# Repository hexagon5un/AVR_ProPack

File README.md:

# AVR ProPack

(rhymes with Kropak.  Yummm...)

## Simple Circuit Bits to Help Your Breadboarding

Preliminary docs up at http://littlehacks.org/propack

At the moment, everything's in a state of beta.  You're welcome to try anything out.

I'm going to make a run of these boards soon enough in the future.  If you're interested, let me know.

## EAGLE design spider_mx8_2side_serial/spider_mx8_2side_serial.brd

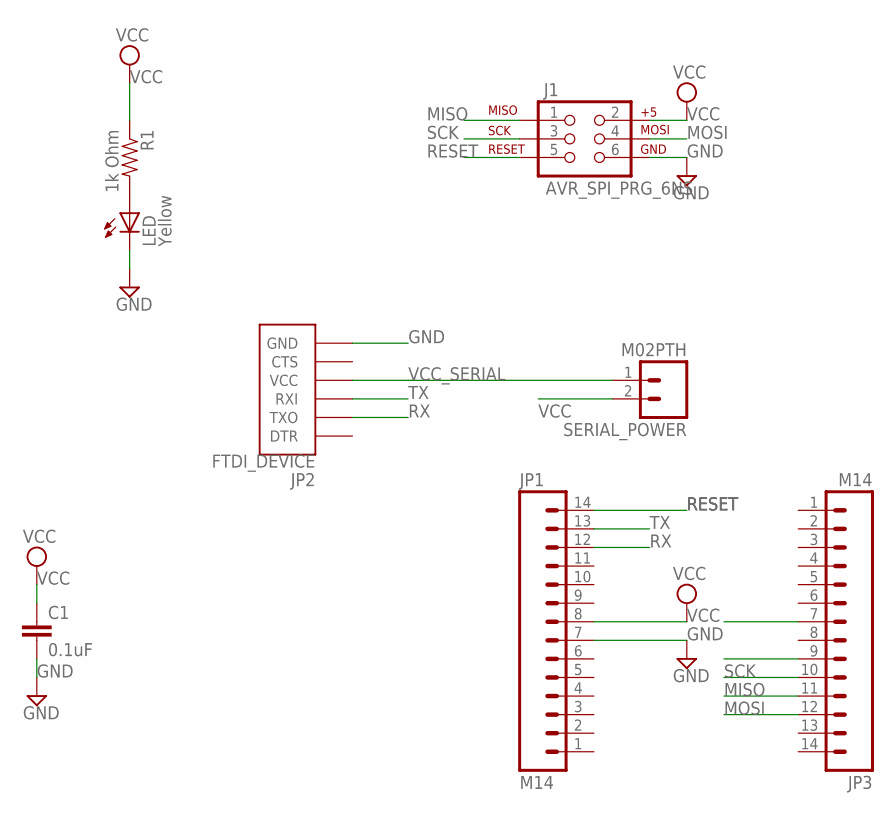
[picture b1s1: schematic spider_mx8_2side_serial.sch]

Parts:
C1: 0.1uF; 1206
J1: AVR_SPI_PRG_6NS; 2X3-NS
JP1, JP3: M14; 1X14
JP2: FTDI_DEVICE; FTDI_DEVICE_SIDE
LED: Yellow; LED-1206
R1: 1k Ohm; 1206
SERIAL_POWER: M02PTH; 1X02

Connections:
GND: C1.2, J1.6, JP1.7, JP2.P$6 (GND), JP3.7, LED.C
MISO: J1.1, JP3.11
MOSI: J1.4, JP3.12
unnamed: LED.A, R1.2
RESET: J1.5, JP1.14
RX: JP1.12, JP2.P$2 (TXO)
SCK: J1.3, JP3.10
TX: JP1.13, JP2.P$3 (RXI)
VCC: C1.1, J1.2, JP1.8, JP3.9, R1.1, SERIAL_POWER.2
VCC_SERIAL: JP2.P$4 (VCC), SERIAL_POWER.1

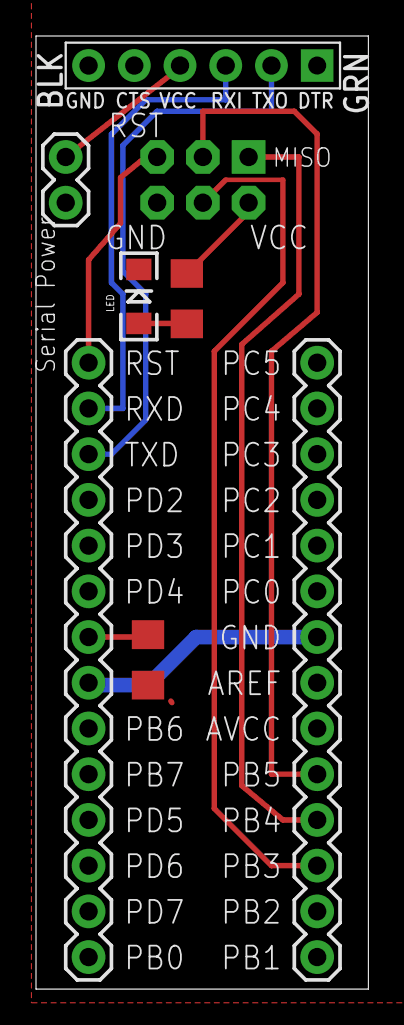
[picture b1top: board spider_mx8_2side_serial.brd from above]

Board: 2 copper layers, 18.5 x 52.9 mm, 8 parts (0 on the bottom side), 10 nets.

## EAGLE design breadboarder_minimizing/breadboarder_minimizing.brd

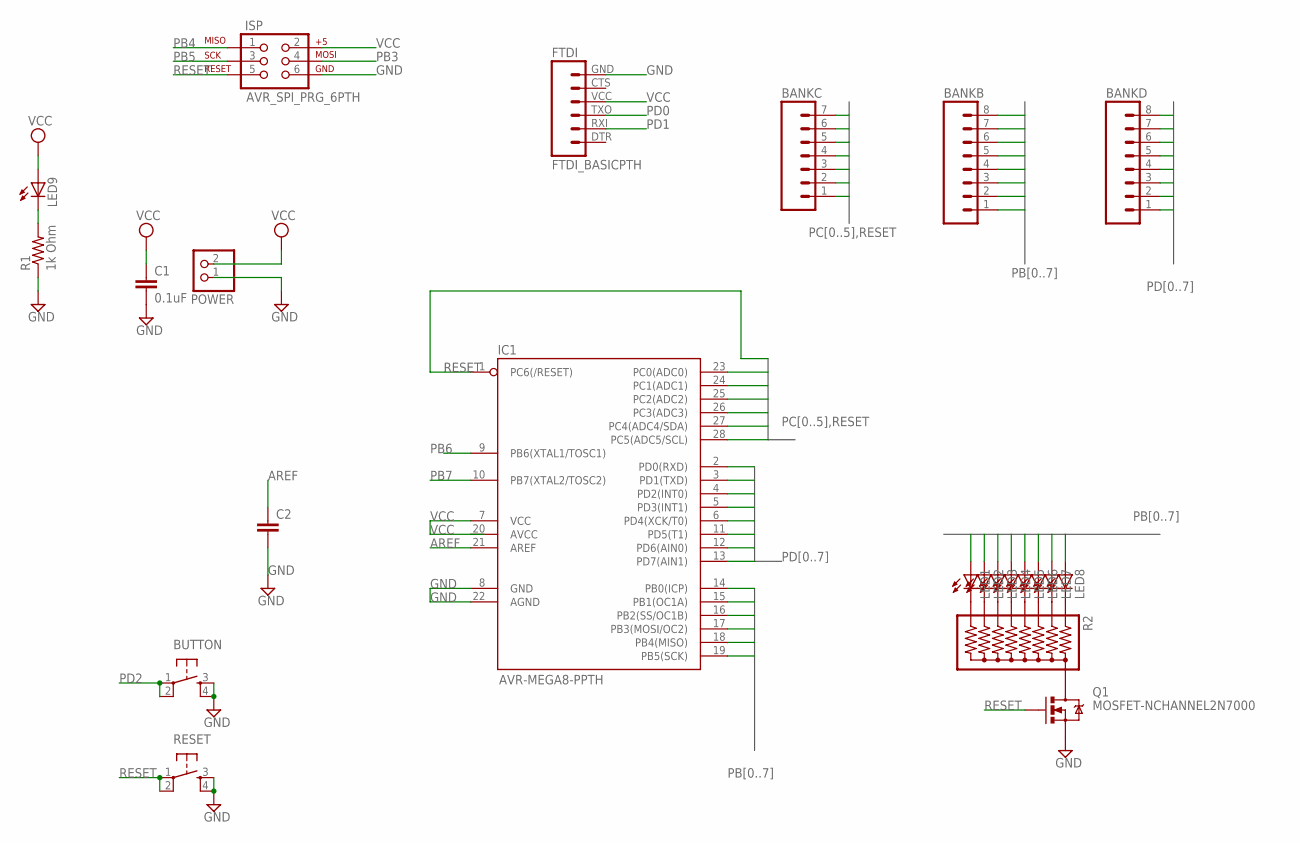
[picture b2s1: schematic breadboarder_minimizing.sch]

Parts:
BANKB: M08LONGPADS; 1X08_LONGPADS
BANKC: M07LONGPADS; 1X07_LONGPADS
BANKD: M08LONGPADS; 1X08_LONGPADS
BUTTON: TAC_SWITCHPTH; TACTILE-PTH
C1: 0.1uF; CAP-PTH-SMALL-KIT
C2: CAPKIT; CAP-PTH-SMALL-KIT
FTDI: FTDI_BASICPTH; FTDI_BASIC
IC1: AVR-MEGA8-PPTH; DIL28-3
ISP: AVR_SPI_PRG_6PTH; 2X3
LED1, LED2, LED3, LED4, LED5, LED6, LED7, LED8, LED9: LED3MM
POWER: PINHD-1X2; 1X02
Q1: MOSFET-NCHANNEL2N7000; TO-92
R1: 1k Ohm; AXIAL-0.3
R2: RPACK-BUSSED-8SIP-PTH-8-LP; RPACK-SIP-PTH-8-LP
RESET: TAC_SWITCHPTH; TACTILE-PTH

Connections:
AREF: C2.1, IC1.21 (AREF)
GND: BUTTON.3, BUTTON.4, C1.2, C2.2, FTDI.GND (6), IC1.8 (GND), IC1.22 (AGND), ISP.6, POWER.1, Q1.1 (S), R1.P$1 (1), RESET.3, RESET.4
unnamed: Q1.3 (D), R2.P$1 (1)
unnamed: LED1.K (C), R2.P$9 (9)
unnamed: LED2.K (C), R2.P$8 (8)
unnamed: LED3.K (C), R2.P$7 (7)
unnamed: LED4.K (C), R2.P$6 (6)
unnamed: LED5.K (C), R2.P$5 (5)
unnamed: LED6.K (C), R2.P$4 (4)
unnamed: LED7.K (C), R2.P$3 (3)
unnamed: LED8.K (C), R2.P$2 (2)
unnamed: LED9.K (C), R1.P$2 (2)
PB0: BANKB.8, IC1.14 (PB0(ICP)), LED1.A
PB1: BANKB.7, IC1.15 (PB1(OC1A)), LED2.A
PB2: BANKB.6, IC1.16 (PB2(SS/OC1B)), LED3.A
PB3: BANKB.5, IC1.17 (PB3(MOSI/OC2)), ISP.4, LED4.A
PB4: BANKB.4, IC1.18 (PB4(MISO)), ISP.1, LED5.A
PB5: BANKB.3, IC1.19 (PB5(SCK)), ISP.3, LED6.A
PB6: BANKB.2, IC1.9 (PB6(XTAL1/TOSC1)), LED7.A
PB7: BANKB.1, IC1.10 (PB7(XTAL2/TOSC2)), LED8.A
PC0: BANKC.7, IC1.23 (PC0(ADC0))
PC1: BANKC.6, IC1.24 (PC1(ADC1))
PC2: BANKC.5, IC1.25 (PC2(ADC2))
PC3: BANKC.4, IC1.26 (PC3(ADC3))
PC4: BANKC.3, IC1.27 (PC4(ADC4/SDA))
PC5: BANKC.2, IC1.28 (PC5(ADC5/SCL))
PD0: BANKD.8, FTDI.TXO (3), IC1.2 (PD0(RXD))
PD1: BANKD.7, FTDI.RXI (2), IC1.3 (PD1(TXD))
PD2: BANKD.6, BUTTON.1, BUTTON.2, IC1.4 (PD2(INT0))
PD3: BANKD.5, IC1.5 (PD3(INT1))
PD4: BANKD.4, IC1.6 (PD4(XCK/T0))
PD5: BANKD.3, IC1.11 (PD5(T1))
PD6: BANKD.2, IC1.12 (PD6(AIN0))
PD7: BANKD.1, IC1.13 (PD7(AIN1))
RESET: BANKC.1, IC1.1 (PC6(/RESET)), ISP.5, Q1.2 (G), RESET.1, RESET.2
VCC: C1.1, FTDI.VCC (4), IC1.7 (VCC), ISP.2, LED9.A, POWER.2

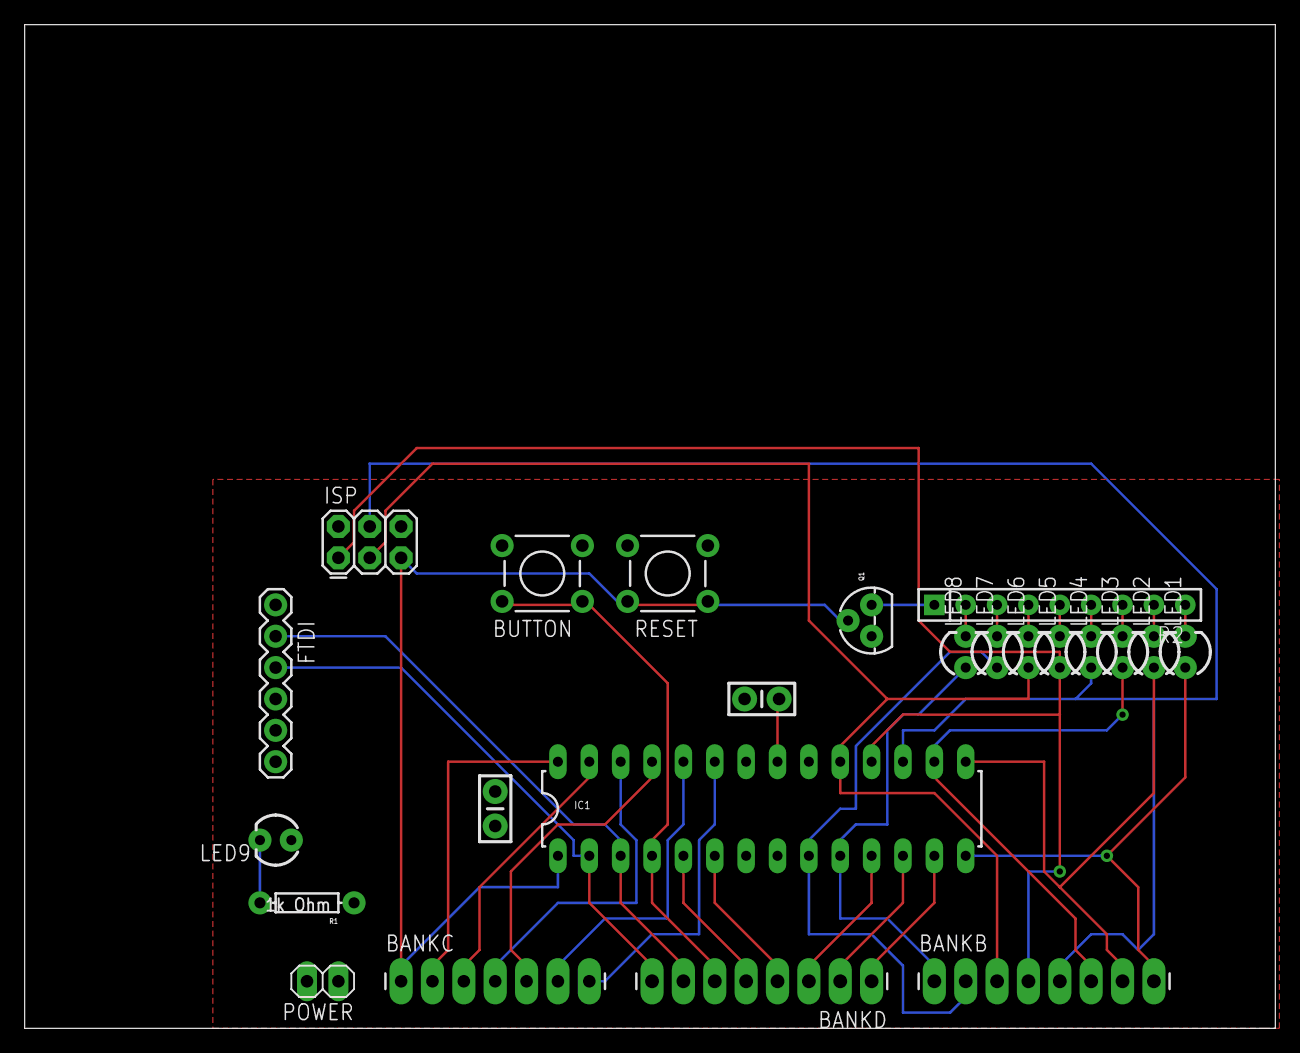
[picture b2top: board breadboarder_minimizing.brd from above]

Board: 2 copper layers, 101.3 x 81.3 mm, 23 parts (0 on the bottom side), 36 nets.

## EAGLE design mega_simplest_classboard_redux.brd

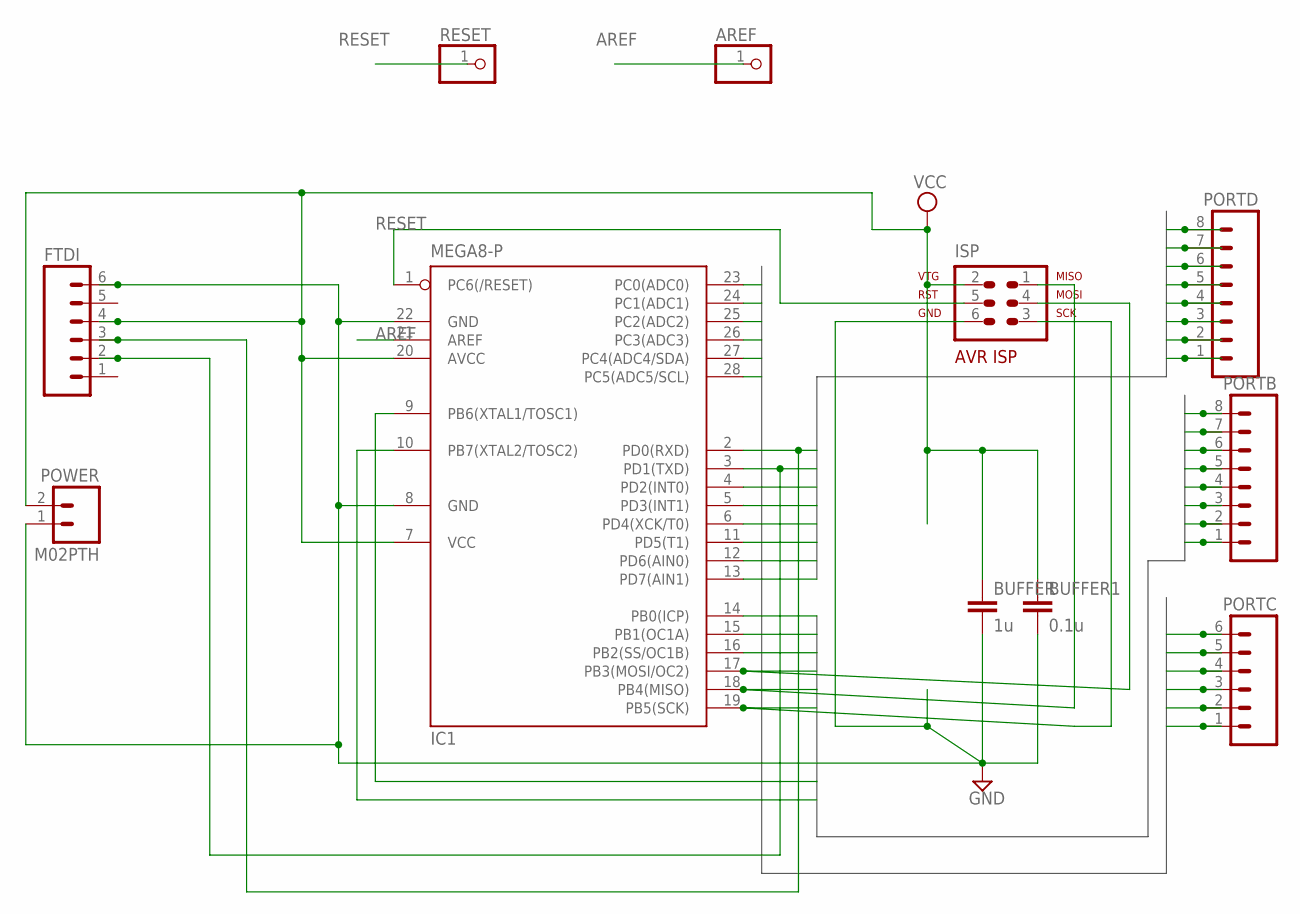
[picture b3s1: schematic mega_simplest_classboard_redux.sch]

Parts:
AREF: PINHD-1X1; 1X01
BUFFER: 1u; C5B3.5
BUFFER1: 0.1u; C5B3.5
FTDI: M06SIP; 1X06
IC1: MEGA8-P; DIL28-3
ISP: AVR-ISP-6
PORTB: M081X08; 1X08
PORTC: M06SIP; 1X06
PORTD: M081X08; 1X08
POWER: M02PTH; 1X02
RESET: PINHD-1X1; 1X01

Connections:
AREF: AREF.1, IC1.21 (AREF)
GND: BUFFER.2, BUFFER1.2, FTDI.6, IC1.8 (GND), IC1.22 (GND), ISP.6, POWER.1
PORTB0: IC1.14 (PB0(ICP)), PORTB.8
PORTB1: IC1.15 (PB1(OC1A)), PORTB.7
PORTB2: IC1.16 (PB2(SS/OC1B)), PORTB.6
PORTB3: IC1.17 (PB3(MOSI/OC2)), ISP.4, PORTB.5
PORTB4: IC1.18 (PB4(MISO)), ISP.1, PORTB.4
PORTB5: IC1.19 (PB5(SCK)), ISP.3, PORTB.3
PORTB6: IC1.9 (PB6(XTAL1/TOSC1)), PORTB.2
PORTB7: IC1.10 (PB7(XTAL2/TOSC2)), PORTB.1
PORTC0: IC1.23 (PC0(ADC0)), PORTC.6
PORTC1: IC1.24 (PC1(ADC1)), PORTC.5
PORTC2: IC1.25 (PC2(ADC2)), PORTC.4
PORTC3: IC1.26 (PC3(ADC3)), PORTC.3
PORTC4: IC1.27 (PC4(ADC4/SDA)), PORTC.2
PORTC5: IC1.28 (PC5(ADC5/SCL)), PORTC.1
PORTD0: FTDI.3, IC1.2 (PD0(RXD)), PORTD.8
PORTD1: FTDI.2, IC1.3 (PD1(TXD)), PORTD.7
PORTD2: IC1.4 (PD2(INT0)), PORTD.6
PORTD3: IC1.5 (PD3(INT1)), PORTD.5
PORTD4: IC1.6 (PD4(XCK/T0)), PORTD.4
PORTD5: IC1.11 (PD5(T1)), PORTD.3
PORTD6: IC1.12 (PD6(AIN0)), PORTD.2
PORTD7: IC1.13 (PD7(AIN1)), PORTD.1
RESET: IC1.1 (PC6(/RESET)), ISP.5, RESET.1
VCC: BUFFER.1, BUFFER1.1, FTDI.4, IC1.7 (VCC), IC1.20 (AVCC), ISP.2, POWER.2

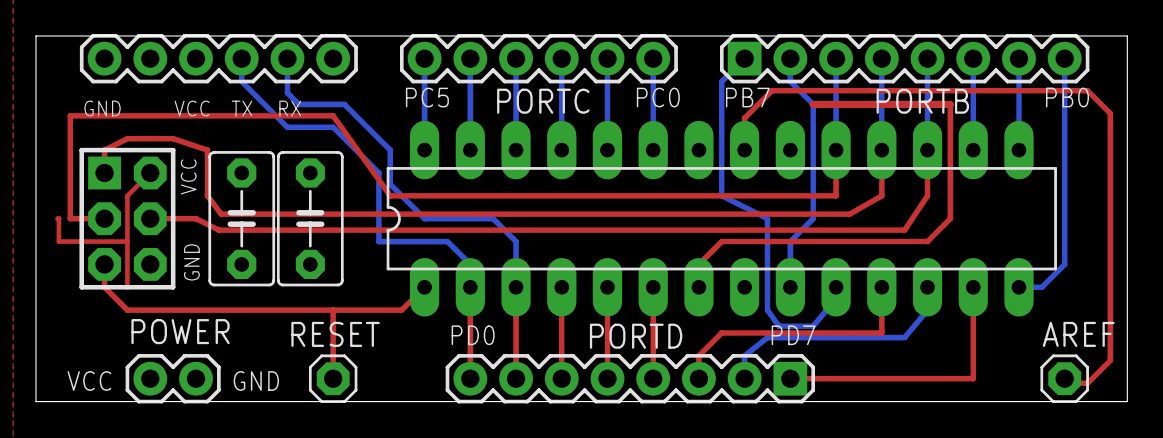
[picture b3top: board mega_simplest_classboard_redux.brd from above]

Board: 2 copper layers, 60.6 x 20.3 mm, 11 parts (0 on the bottom side), 26 nets.

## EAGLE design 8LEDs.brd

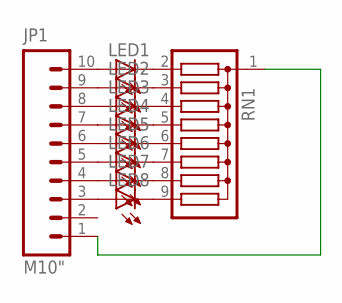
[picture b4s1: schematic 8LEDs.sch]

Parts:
JP1: M10"; 1X10
LED1, LED2, LED3, LED4, LED5, LED6, LED7, LED8: LED5MM
RN1: G08R; SIL9

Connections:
GND: JP1.1, RN1.1
unnamed: LED1.K (C), RN1.2
unnamed: LED2.K (C), RN1.3
unnamed: LED3.K (C), RN1.4
unnamed: LED4.K (C), RN1.5
unnamed: LED5.K (C), RN1.6
unnamed: LED6.K (C), RN1.7
unnamed: LED7.K (C), RN1.8
unnamed: LED8.K (C), RN1.9
unnamed: JP1.10, LED1.A
unnamed: JP1.9, LED2.A
unnamed: JP1.8, LED3.A
unnamed: JP1.7, LED4.A
unnamed: JP1.6, LED5.A
unnamed: JP1.5, LED6.A
unnamed: JP1.4, LED7.A
unnamed: JP1.3, LED8.A

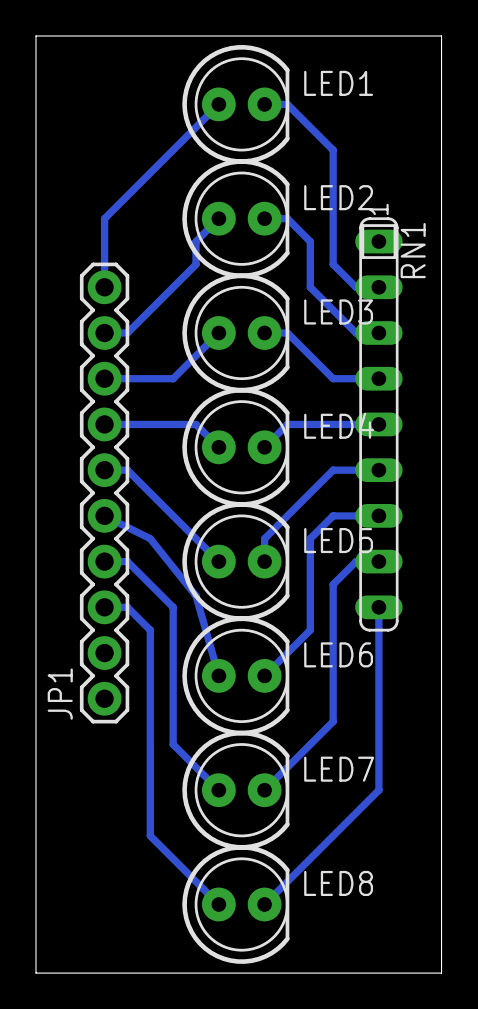
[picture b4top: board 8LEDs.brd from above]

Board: 2 copper layers, 22.5 x 52.1 mm, 10 parts (0 on the bottom side), 17 nets.

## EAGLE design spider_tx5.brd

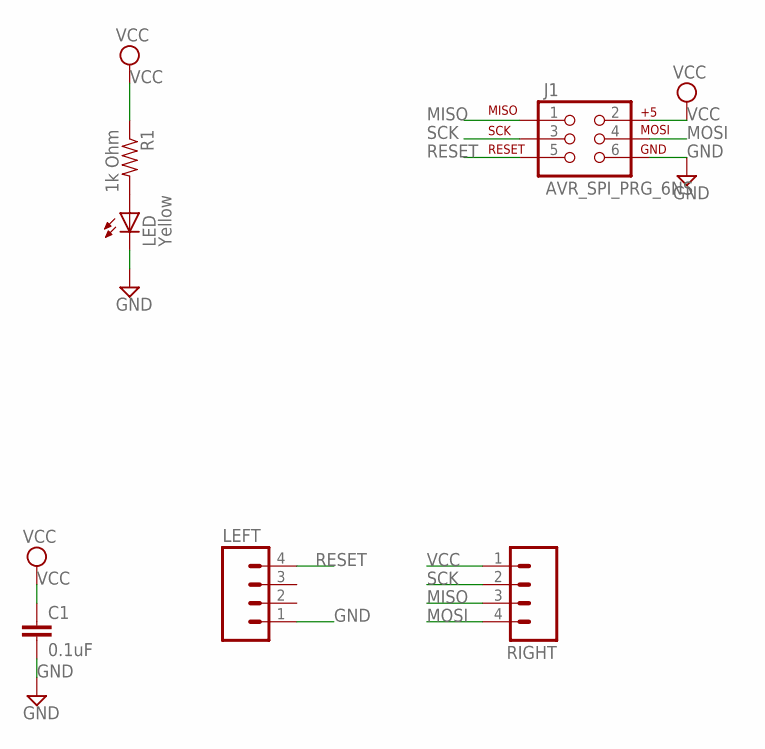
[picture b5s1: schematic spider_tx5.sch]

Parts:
C1: 0.1uF; 1206
J1: AVR_SPI_PRG_6NS; 2X3-NS
LED: Yellow; LED-1206
LEFT: M04PTH; 1X04
R1: 1k Ohm; 1206
RIGHT: M04PTH; 1X04

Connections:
GND: C1.2, J1.6, LED.C, LEFT.1
MISO: J1.1, RIGHT.3
MOSI: J1.4, RIGHT.4
unnamed: LED.A, R1.2
RESET: J1.5, LEFT.4
SCK: J1.3, RIGHT.2
VCC: C1.1, J1.2, R1.1, RIGHT.1

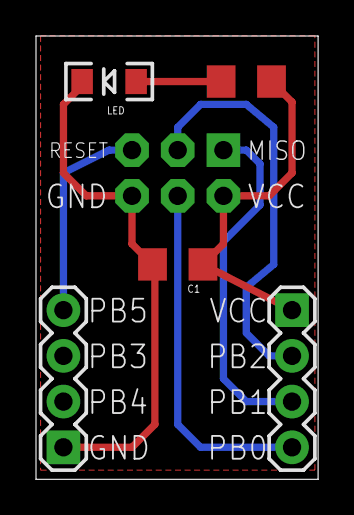
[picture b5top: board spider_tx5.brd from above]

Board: 2 copper layers, 15.7 x 24.6 mm, 6 parts (0 on the bottom side), 7 nets.

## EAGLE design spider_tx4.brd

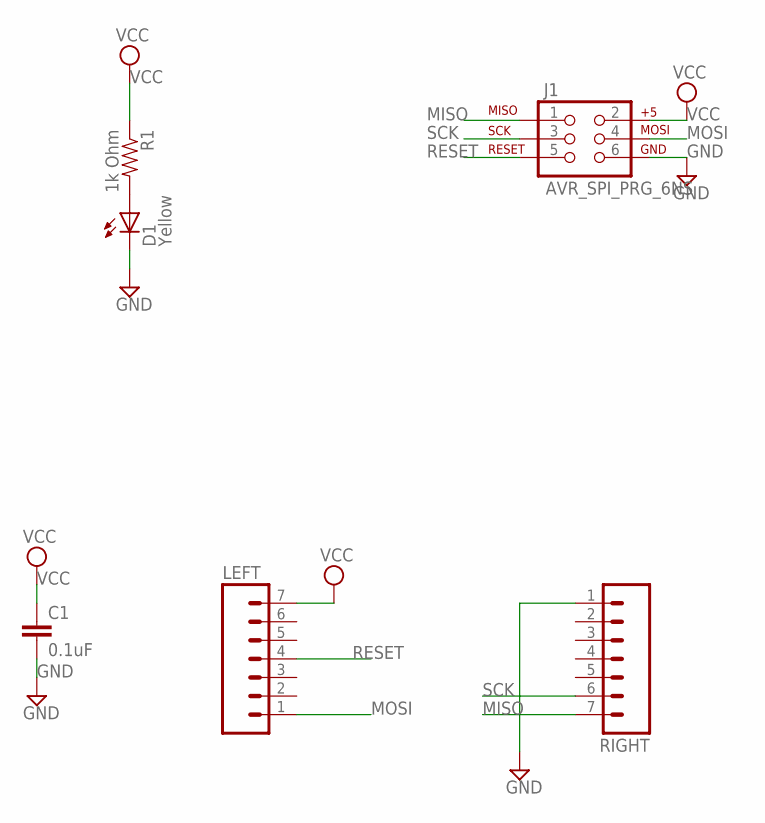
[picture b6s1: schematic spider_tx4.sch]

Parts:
C1: 0.1uF; 1206
D1: Yellow; LED-1206
J1: AVR_SPI_PRG_6NS; 2X3-NS
LEFT: M07; 1X07
R1: 1k Ohm; 1206
RIGHT: M07; 1X07

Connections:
GND: C1.2, D1.C, J1.6, RIGHT.1
MISO: J1.1, RIGHT.7
MOSI: J1.4, LEFT.1
unnamed: D1.A, R1.2
RESET: J1.5, LEFT.4
SCK: J1.3, RIGHT.6
VCC: C1.1, J1.2, LEFT.7, R1.1

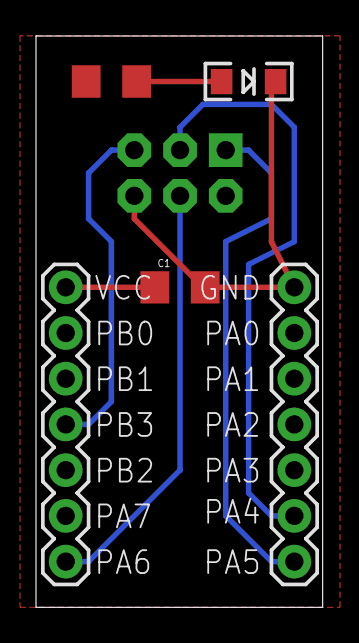
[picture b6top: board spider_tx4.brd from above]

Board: 2 copper layers, 15.9 x 31.7 mm, 6 parts (0 on the bottom side), 7 nets.

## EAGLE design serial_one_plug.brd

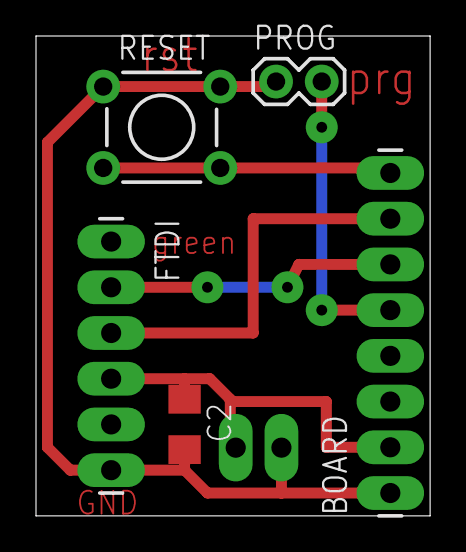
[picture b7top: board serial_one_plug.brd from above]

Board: 2 copper layers, 21.9 x 26.7 mm, 6 parts (0 on the bottom side), 6 nets.

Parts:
BOARD: 1X08_LONGPADS
C2: 0.1 uF; C1206
FTDI: 1X06_LONGPADS
POWER_RAIL: M02PTH3; 1X02_LONGPADS
PROG: M02PTH; 1X02
RESET: TACTILE-PTH

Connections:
GND: BOARD.1, C2.2, FTDI.6, POWER_RAIL.1, PROG.1, RESET.1, RESET.2
PD2: BOARD.5, PROG.2
RESET: BOARD.8, RESET.3, RESET.4
RX: BOARD.6, FTDI.2
TX: BOARD.7, FTDI.3
VCC: BOARD.2, C2.1, FTDI.4, POWER_RAIL.2

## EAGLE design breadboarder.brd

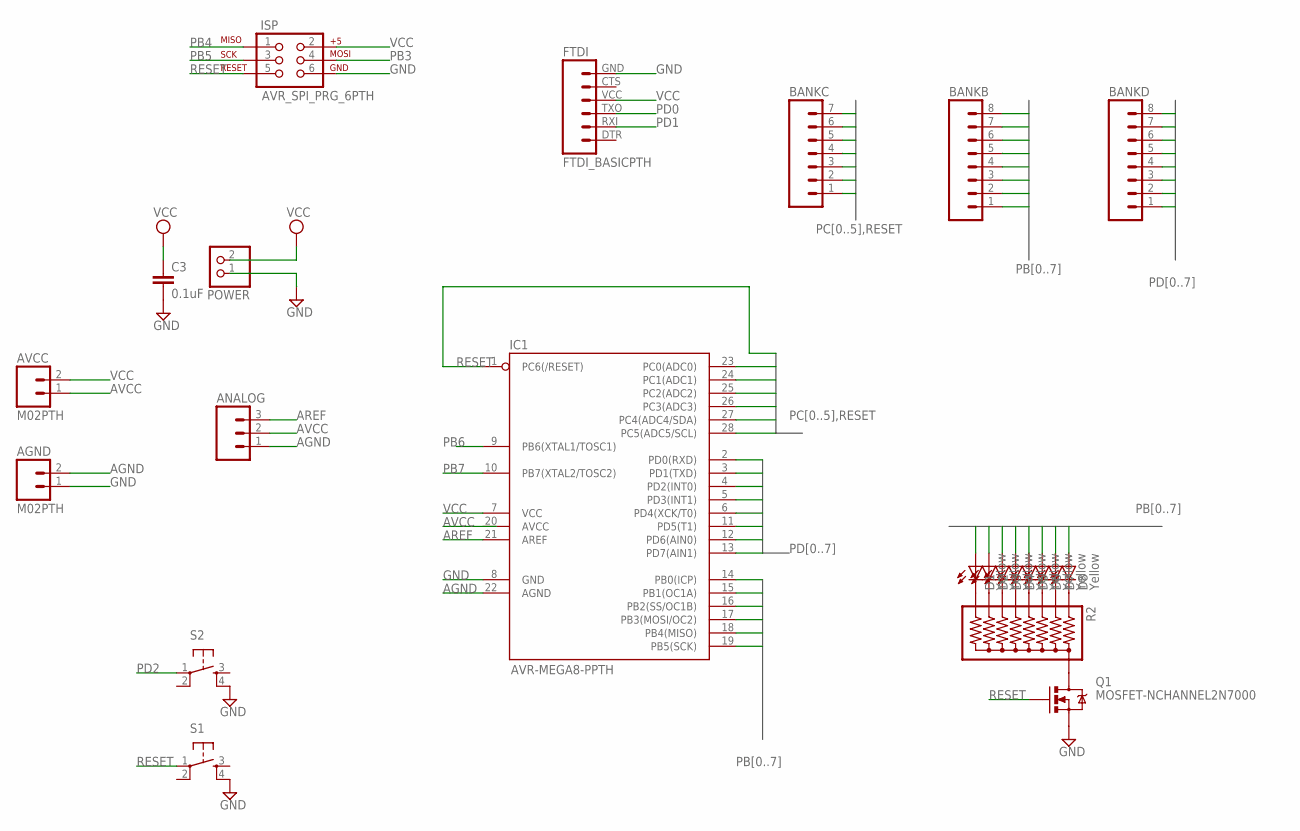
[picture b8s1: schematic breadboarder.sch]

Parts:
AGND: M02PTH; 1X02
ANALOG: M03LONGPADS; 1X03_LONGPADS
AVCC: M02PTH; 1X02
BANKB: M08LONGPADS; 1X08_LONGPADS
BANKC: M07LONGPADS; 1X07_LONGPADS
BANKD: M08LONGPADS; 1X08_LONGPADS
C3: 0.1uF; C1206
D1, D2, D3, D4, D5, D6, D7, D8: Yellow; LED-1206
FTDI: FTDI_BASICPTH; FTDI_BASIC
IC1: AVR-MEGA8-PPTH; DIL28-3
ISP: AVR_SPI_PRG_6PTH; 2X3
POWER: PINHD-1X2; 1X02
Q1: MOSFET-NCHANNEL2N7000; TO-92
R2: RPACK-BUSSED-8SIP-PTH-8-LP; RPACK-SIP-PTH-8-LP
S1, S2: TAC_SWITCHPTH; TACTILE-PTH

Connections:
AGND: AGND.2, ANALOG.1, IC1.22 (AGND)
AREF: ANALOG.3, IC1.21 (AREF)
AVCC: ANALOG.2, AVCC.1
GND: AGND.1, C3.2, FTDI.GND (6), IC1.8 (GND), ISP.6, POWER.1, Q1.1 (S), S1.4, S2.4
unnamed: Q1.3 (D), R2.P$1 (1)
unnamed: D2.C, R2.P$8 (8)
unnamed: D3.C, R2.P$7 (7)
unnamed: D4.C, R2.P$6 (6)
unnamed: D5.C, R2.P$5 (5)
unnamed: D6.C, R2.P$4 (4)
unnamed: D7.C, R2.P$3 (3)
unnamed: D8.C, R2.P$2 (2)
unnamed: D1.C, R2.P$9 (9)
PB0: BANKB.8, D1.A, IC1.14 (PB0(ICP))
PB1: BANKB.7, D2.A, IC1.15 (PB1(OC1A))
PB2: BANKB.6, D3.A, IC1.16 (PB2(SS/OC1B))
PB3: BANKB.5, D4.A, IC1.17 (PB3(MOSI/OC2)), ISP.4
PB4: BANKB.4, D5.A, IC1.18 (PB4(MISO)), ISP.1
PB5: BANKB.3, D6.A, IC1.19 (PB5(SCK)), ISP.3
PB6: BANKB.2, D7.A, IC1.9 (PB6(XTAL1/TOSC1))
PB7: BANKB.1, D8.A, IC1.10 (PB7(XTAL2/TOSC2))
PC0: BANKC.7, IC1.23 (PC0(ADC0))
PC1: BANKC.6, IC1.24 (PC1(ADC1))
PC2: BANKC.5, IC1.25 (PC2(ADC2))
PC3: BANKC.4, IC1.26 (PC3(ADC3))
PC4: BANKC.3, IC1.27 (PC4(ADC4/SDA))
PC5: BANKC.2, IC1.28 (PC5(ADC5/SCL))
PD0: BANKD.8, FTDI.TXO (3), IC1.2 (PD0(RXD))
PD1: BANKD.7, FTDI.RXI (2), IC1.3 (PD1(TXD))
PD2: BANKD.6, IC1.4 (PD2(INT0)), S2.1
PD3: BANKD.5, IC1.5 (PD3(INT1))
PD4: BANKD.4, IC1.6 (PD4(XCK/T0))
PD5: BANKD.3, IC1.11 (PD5(T1))
PD6: BANKD.2, IC1.12 (PD6(AIN0))
PD7: BANKD.1, IC1.13 (PD7(AIN1))
RESET: BANKC.1, IC1.1 (PC6(/RESET)), ISP.5, Q1.2 (G), S1.1
VCC: AVCC.2, C3.1, FTDI.VCC (4), IC1.7 (VCC), ISP.2, POWER.2

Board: 2 copper layers, 23 parts (0 on the bottom side), 37 nets, no tracks yet.

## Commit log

2014-02-21 first draft of megaxx8 spider
    no cap, no LED
2014-02-21 added led and cap. noticed all on bottom side
    so I'll need to re-do all this with at least SMT parts on the top
    if I want to keep it quasi-one-layer, I'll need to flip wires to top
    too. boo.
2014-02-21 moved everything to topside
    still two vias, and has AVR footprint
    next step, can I get a more compact layout by dropping the AVR?
2014-02-21 printed version take one
    needs labels, get rid of AVR
    see if I can solve the two vias. (probbly not)
2014-02-21 thinner, double-sided board, no vias (no labels yet)
2014-02-21 printed this version out. works. sexy.
2014-02-21 untested, but probably good 2sided board
    using thin pins. need to check DRC for whatever foundry use
    (esp the edge-routing may give trouble)
    (also, the label layer on the bottom side. think gold phoenix doesn't
    do that.)
2014-02-21 printed version of serial adapter. boo.
    trying again with the wires on the "top" layer -- will allow
    it to connect up using straight pins, but at a right-angle at the edge
    of the board. will be awesome.
2014-02-21 starting work on the breadboarder
    at the moment, just placing parts. still incomplete.
2014-02-21 think I've got all of breadboarder parts down
    ...but who knows.
2014-02-21 lol. first try = sucessful autoroute
    now comes the process of refinement...
2014-02-22 two new board variants, each getting less complicated
2014-02-22 bug with led fet fixed
    now can pull to reset line or ground(!), disabling LEDs
2014-02-22 serial plug version 2 -- reset + prog
    added more (more more!) functionality to the serial plug
    has a ground jumper for PD2, pushbutton on reset
    enabling it to work with bootloader
    printed out, run, it's great.
2014-02-22 shrunk cap on serial board to 1206 from 1210
2014-02-22 first draft of 2-sided spider for tinyx4 series
    untested, but should work, right?
    made to sparkfun's dru
2014-02-23 noticed bug in board spidertx4. fixed. still tweaking.
2014-02-23 tweaked tx4 spider to death. printing and testing.
2014-02-23 mx8 spider, two-sided built and tested
2014-03-03 pulled in two designs from the past
    worked the simple one over a bunch: this is the printed-out version
    also some tweaks on the original classboard -- but overall very much the
    same. (might be production-ready)
2014-03-03 added tiny45 spider, mx8 spider with serial
    difference between spider with serial and full-fledged programmer board?
    only the pin layout
2014-03-04 tested version minimal classboard
    is it a minimal classboard or a mega breadboarder?
    8-LED breakout untested, mostly-symmetric design
2014-03-17 added power jumper to serial: mx8 spider
    other tweaks include stuff with the 8LED modules
2014-03-17 What a mess. Moved everything into own subdir
2014-03-17 new readme
2014-03-17 work on readme
2014-08-21 cleanup -- renaming to match website
    and deleting the stuff I don't use
2014-08-21 added inliner, more top text
2014-08-21 more ignored files
2014-08-21 added panelizing
    first run-through using gerbmerge
    there's a bunch of dirty details in panel.cfg
    viewGerb is a quick script to open gerbers in the right order
2014-08-21 updated gitignore to cover more gerbers

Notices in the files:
parts and their libraries:
SparkFun-LED: Licensing: CC v3.0 Share-Alike You are welcome to use this library for commercial purposes.
